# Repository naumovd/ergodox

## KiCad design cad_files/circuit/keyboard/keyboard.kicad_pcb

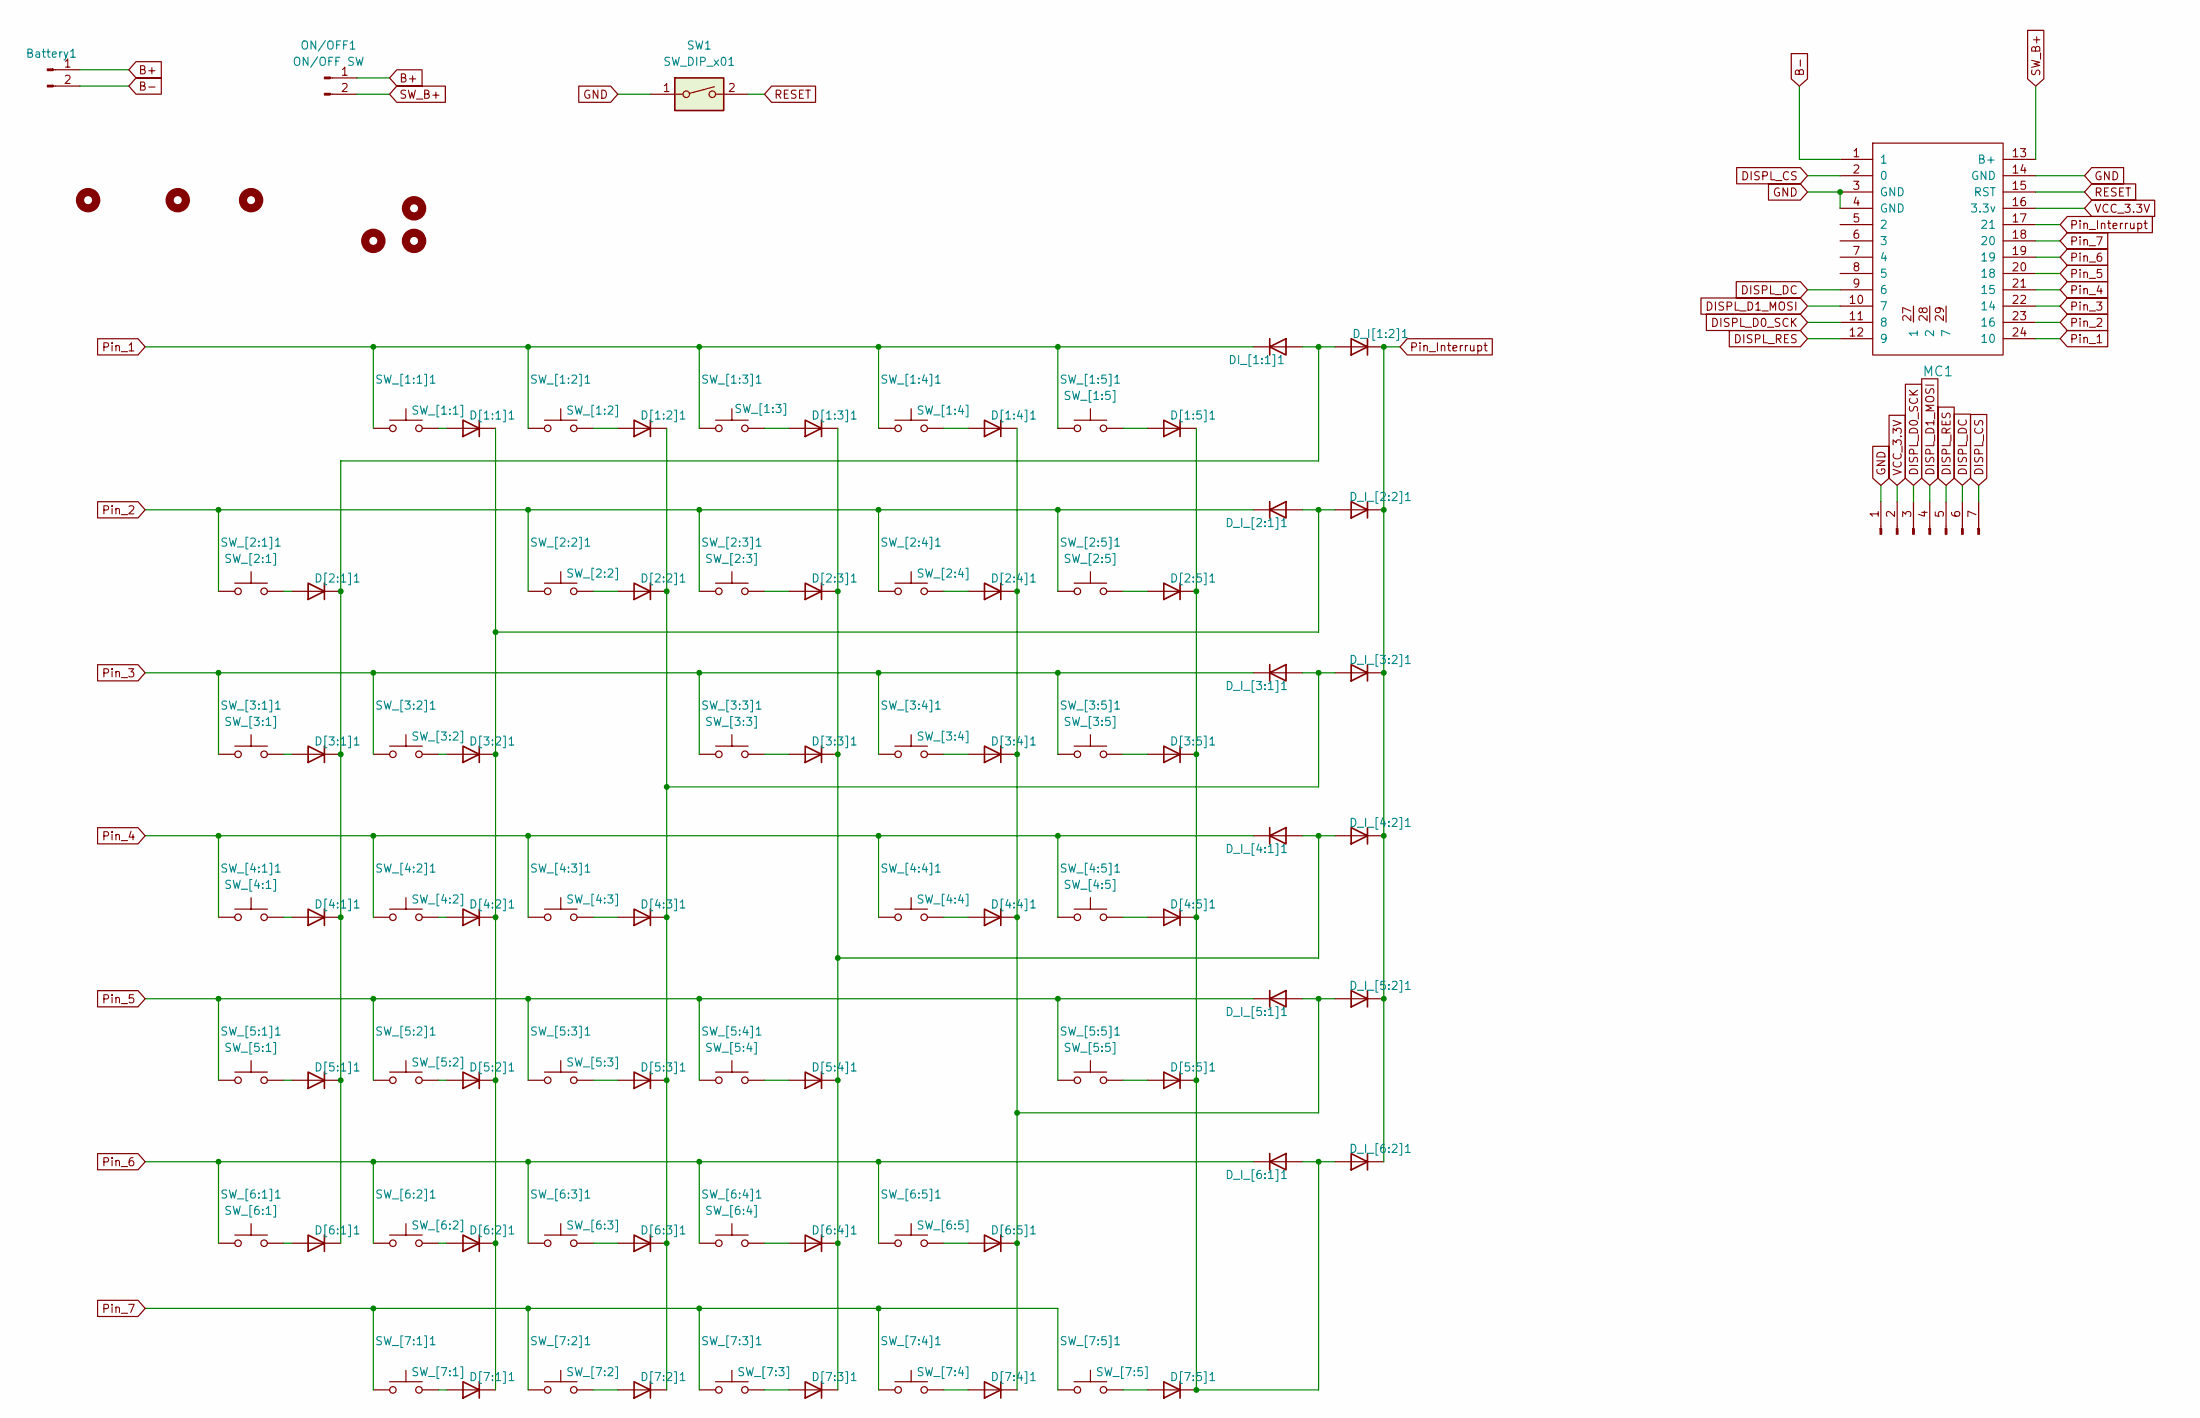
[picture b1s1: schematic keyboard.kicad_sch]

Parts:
Battery1: JST_PH_B2B-PH-K_1x02_P2.00mm_Vertical
DI_[1:1]1: Diode; D_T-1_P5.08mm_Horizontal
D[1:1]1, D[1:2]1, D[1:3]1, D[1:4]1, D[1:5]1, D[2:1]1, D[2:2]1, D[2:3]1, D[2:4]1, D[2:5]1, D[3:1]1, D[3:2]1, D[3:3]1, D[3:4]1, D[3:5]1, D[4:1]1, D[4:2]1, D[4:3]1, D[4:4]1, D[4:5]1, D[5:1]1, D[5:2]1, D[5:3]1, D[5:4]1, D[5:5]1, D[6:1]1, D[6:2]1, D[6:3]1, D[6:4]1, D[6:5]1, D[7:1]1, D[7:2]1, D[7:3]1, D[7:4]1, D[7:5]1: Diode; D_T-1_P5.08mm_Horizontal
D_I[1:2]1: Diode; D_T-1_P5.08mm_Horizontal
D_I_[2:1]1, D_I_[2:2]1, D_I_[3:1]1, D_I_[3:2]1, D_I_[4:1]1, D_I_[4:2]1, D_I_[5:1]1, D_I_[5:2]1, D_I_[6:1]1, D_I_[6:2]1: Diode; D_T-1_P5.08mm_Horizontal
Display1: PinHeader_1x07_P2.00mm_Vertical
H1, H2, H3, H5, H6, H7: MountingHole; MountingHole_2.2mm_M2_DIN965_Pad
MC1: Nice_Nano_V2; nice_nano_H_USBup
ON/OFF1: ON/OFF SW; JST_PH_B2B-PH-K_1x02_P2.00mm_Vertical
SW1: SW_DIP_x01; SW_PUSH_6mm_H4.3mm
SW_[1:1]1: SW_[1:1]; SW_MX_HS_KS-2P02B01-01_1u
SW_[1:2]1: SW_[1:2]; SW_MX_HS_KS-2P02B01-01_1u
SW_[1:3]1: SW_[1:3]; SW_MX_HS_KS-2P02B01-01_1u
SW_[1:4]1: SW_[1:4]; SW_MX_HS_KS-2P02B01-01_1u
SW_[1:5]1: SW_[1:5]; SW_MX_HS_KS-2P02B01-01_1u
SW_[2:1]1: SW_[2:1]; SW_MX_HS_KS-2P02B01-01_1u
SW_[2:2]1: SW_[2:2]; SW_MX_HS_KS-2P02B01-01_1u
SW_[2:3]1: SW_[2:3]; SW_MX_HS_KS-2P02B01-01_1u
SW_[2:4]1: SW_[2:4]; SW_MX_HS_KS-2P02B01-01_1u
SW_[2:5]1: SW_[2:5]; SW_MX_HS_KS-2P02B01-01_1u
SW_[3:1]1: SW_[3:1]; SW_MX_HS_KS-2P02B01-01_1u
SW_[3:2]1: SW_[3:2]; SW_MX_HS_KS-2P02B01-01_1u
SW_[3:3]1: SW_[3:3]; SW_MX_HS_KS-2P02B01-01_1u
SW_[3:4]1: SW_[3:4]; SW_MX_HS_KS-2P02B01-01_1u
SW_[3:5]1: SW_[3:5]; SW_MX_HS_KS-2P02B01-01_1u
SW_[4:1]1: SW_[4:1]; SW_MX_HS_KS-2P02B01-01_1u
SW_[4:2]1: SW_[4:2]; SW_MX_HS_KS-2P02B01-01_1u
SW_[4:3]1: SW_[4:3]; SW_MX_HS_KS-2P02B01-01_1u
SW_[4:4]1: SW_[4:4]; SW_MX_HS_KS-2P02B01-01_1u
SW_[4:5]1: SW_[4:5]; SW_MX_HS_KS-2P02B01-01_1u
SW_[5:1]1: SW_[5:1]; SW_MX_HS_KS-2P02B01-01_1u
SW_[5:2]1: SW_[5:2]; SW_MX_HS_KS-2P02B01-01_1u
SW_[5:3]1: SW_[5:3]; SW_MX_HS_KS-2P02B01-01_1u
SW_[5:4]1: SW_[5:4]; SW_MX_HS_KS-2P02B01-01_1u
SW_[5:5]1: SW_[5:5]; SW_MX_HS_KS-2P02B01-01_1u
SW_[6:1]1: SW_[6:1]; SW_MX_HS_KS-2P02B01-01_1u
SW_[6:2]1: SW_[6:2]; SW_MX_HS_KS-2P02B01-01_1u
SW_[6:3]1: SW_[6:3]; SW_MX_HS_KS-2P02B01-01_1u
SW_[6:4]1: SW_[6:4]; SW_MX_HS_KS-2P02B01-01_1u
SW_[6:5]1: SW_[6:5]; SW_MX_HS_KS-2P02B01-01_1u
SW_[7:1]1: SW_[7:1]; SW_MX_HS_KS-2P02B01-01_1u
SW_[7:2]1: SW_[7:2]; SW_MX_HS_KS-2P02B01-01_1u
SW_[7:3]1: SW_[7:3]; SW_MX_HS_KS-2P02B01-01_1u
SW_[7:4]1: SW_[7:4]; SW_MX_HS_KS-2P02B01-01_1u
SW_[7:5]1: SW_[7:5]; SW_MX_HS_KS-2P02B01-01_1u

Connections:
B+: Battery1.1, ON/OFF1.1
B-: Battery1.2, MC1.1; also elsewhere on the board
GND: Display1.1, MC1.3 (GND), MC1.4 (GND), MC1.14 (GND), SW1.1; also elsewhere on the board
unnamed: DI_[1:1]1.2 (A), D[2:1]1.1 (K), D[3:1]1.1 (K), D[4:1]1.1 (K), D[5:1]1.1 (K), D[6:1]1.1 (K), D_I[1:2]1.2 (A)
unnamed: D[1:1]1.2 (A), SW_[1:1]1.2
unnamed: D[1:1]1.1 (K), D[3:2]1.1 (K), D[4:2]1.1 (K), D[5:2]1.1 (K), D[6:2]1.1 (K), D[7:1]1.1 (K), D_I_[2:1]1.2 (A), D_I_[2:2]1.2 (A)
unnamed: D[1:2]1.2 (A), SW_[1:2]1.2
unnamed: D[1:2]1.1 (K), D[2:2]1.1 (K), D[4:3]1.1 (K), D[5:3]1.1 (K), D[6:3]1.1 (K), D[7:2]1.1 (K), D_I_[3:1]1.2 (A), D_I_[3:2]1.2 (A)
unnamed: D[1:3]1.2 (A), SW_[1:3]1.2
unnamed: D[1:3]1.1 (K), D[2:3]1.1 (K), D[3:3]1.1 (K), D[5:4]1.1 (K), D[6:4]1.1 (K), D[7:3]1.1 (K), D_I_[4:1]1.2 (A), D_I_[4:2]1.2 (A)
unnamed: D[1:4]1.2 (A), SW_[1:4]1.2
unnamed: D[1:4]1.1 (K), D[2:4]1.1 (K), D[3:4]1.1 (K), D[4:4]1.1 (K), D[6:5]1.1 (K), D[7:4]1.1 (K), D_I_[5:1]1.2 (A), D_I_[5:2]1.2 (A)
unnamed: D[1:5]1.2 (A), SW_[1:5]1.2
unnamed: D[1:5]1.1 (K), D[2:5]1.1 (K), D[3:5]1.1 (K), D[4:5]1.1 (K), D[5:5]1.1 (K), D[7:5]1.1 (K), D_I_[6:1]1.2 (A), D_I_[6:2]1.2 (A)
unnamed: D[2:1]1.2 (A), SW_[2:1]1.2
unnamed: D[2:2]1.2 (A), SW_[2:2]1.2
unnamed: D[2:3]1.2 (A), SW_[2:3]1.2
unnamed: D[2:4]1.2 (A), SW_[2:4]1.2
unnamed: D[2:5]1.2 (A), SW_[2:5]1.2
unnamed: D[3:1]1.2 (A), SW_[3:1]1.2
unnamed: D[3:2]1.2 (A), SW_[3:2]1.2
unnamed: D[3:3]1.2 (A), SW_[3:3]1.2
unnamed: D[3:4]1.2 (A), SW_[3:4]1.2
unnamed: D[3:5]1.2 (A), SW_[3:5]1.2
unnamed: D[4:1]1.2 (A), SW_[4:1]1.2
unnamed: D[4:2]1.2 (A), SW_[4:2]1.2
unnamed: D[4:3]1.2 (A), SW_[4:3]1.2
unnamed: D[4:4]1.2 (A), SW_[4:4]1.2
unnamed: D[4:5]1.2 (A), SW_[4:5]1.2
unnamed: D[5:1]1.2 (A), SW_[5:1]1.2
unnamed: D[5:2]1.2 (A), SW_[5:2]1.2
unnamed: D[5:3]1.2 (A), SW_[5:3]1.2
unnamed: D[5:4]1.2 (A), SW_[5:4]1.2
unnamed: D[5:5]1.2 (A), SW_[5:5]1.2
unnamed: D[6:1]1.2 (A), SW_[6:1]1.2
unnamed: D[6:2]1.2 (A), SW_[6:2]1.2
unnamed: D[6:3]1.2 (A), SW_[6:3]1.2
unnamed: D[6:4]1.2 (A), SW_[6:4]1.2
unnamed: D[6:5]1.2 (A), SW_[6:5]1.2
unnamed: D[7:1]1.2 (A), SW_[7:1]1.2
unnamed: D[7:2]1.2 (A), SW_[7:2]1.2
unnamed: D[7:3]1.2 (A), SW_[7:3]1.2
unnamed: D[7:4]1.2 (A), SW_[7:4]1.2
unnamed: D[7:5]1.2 (A), SW_[7:5]1.2
unnamed: Display1.2, MC1.16 (3.3v)
unnamed: Display1.3, MC1.11 (8)
unnamed: Display1.4, MC1.10 (7)
unnamed: Display1.5, MC1.12 (9)
unnamed: Display1.6, MC1.9 (6)
unnamed: Display1.7, MC1.2 (0)
Pin_1: DI_[1:1]1.1 (K), MC1.24 (10), SW_[1:1]1.1, SW_[1:2]1.1, SW_[1:3]1.1, SW_[1:4]1.1, SW_[1:5]1.1; also elsewhere on the board
Pin_2: D_I_[2:1]1.1 (K), MC1.23 (16), SW_[2:1]1.1, SW_[2:2]1.1, SW_[2:3]1.1, SW_[2:4]1.1, SW_[2:5]1.1; also elsewhere on the board
Pin_3: D_I_[3:1]1.1 (K), MC1.22 (14), SW_[3:1]1.1, SW_[3:2]1.1, SW_[3:3]1.1, SW_[3:4]1.1, SW_[3:5]1.1; also elsewhere on the board
Pin_4: D_I_[4:1]1.1 (K), MC1.21 (15), SW_[4:1]1.1, SW_[4:2]1.1, SW_[4:3]1.1, SW_[4:4]1.1, SW_[4:5]1.1; also elsewhere on the board
Pin_5: D_I_[5:1]1.1 (K), MC1.20 (18), SW_[5:1]1.1, SW_[5:2]1.1, SW_[5:3]1.1, SW_[5:4]1.1, SW_[5:5]1.1; also elsewhere on the board
Pin_6: D_I_[6:1]1.1 (K), MC1.19, SW_[6:1]1.1, SW_[6:2]1.1, SW_[6:3]1.1, SW_[6:4]1.1, SW_[6:5]1.1; also elsewhere on the board
Pin_7: MC1.18 (20), SW_[7:1]1.1, SW_[7:2]1.1, SW_[7:3]1.1, SW_[7:4]1.1, SW_[7:5]1.1; also elsewhere on the board
Pin_Interrupt: D_I[1:2]1.1 (K), D_I_[2:2]1.1 (K), D_I_[3:2]1.1 (K), D_I_[4:2]1.1 (K), D_I_[5:2]1.1 (K), D_I_[6:2]1.1 (K), MC1.17 (21); also elsewhere on the board
RESET: MC1.15 (RST), SW1.2; also elsewhere on the board
SW_B+: MC1.13 (B+), ON/OFF1.2; also elsewhere on the board

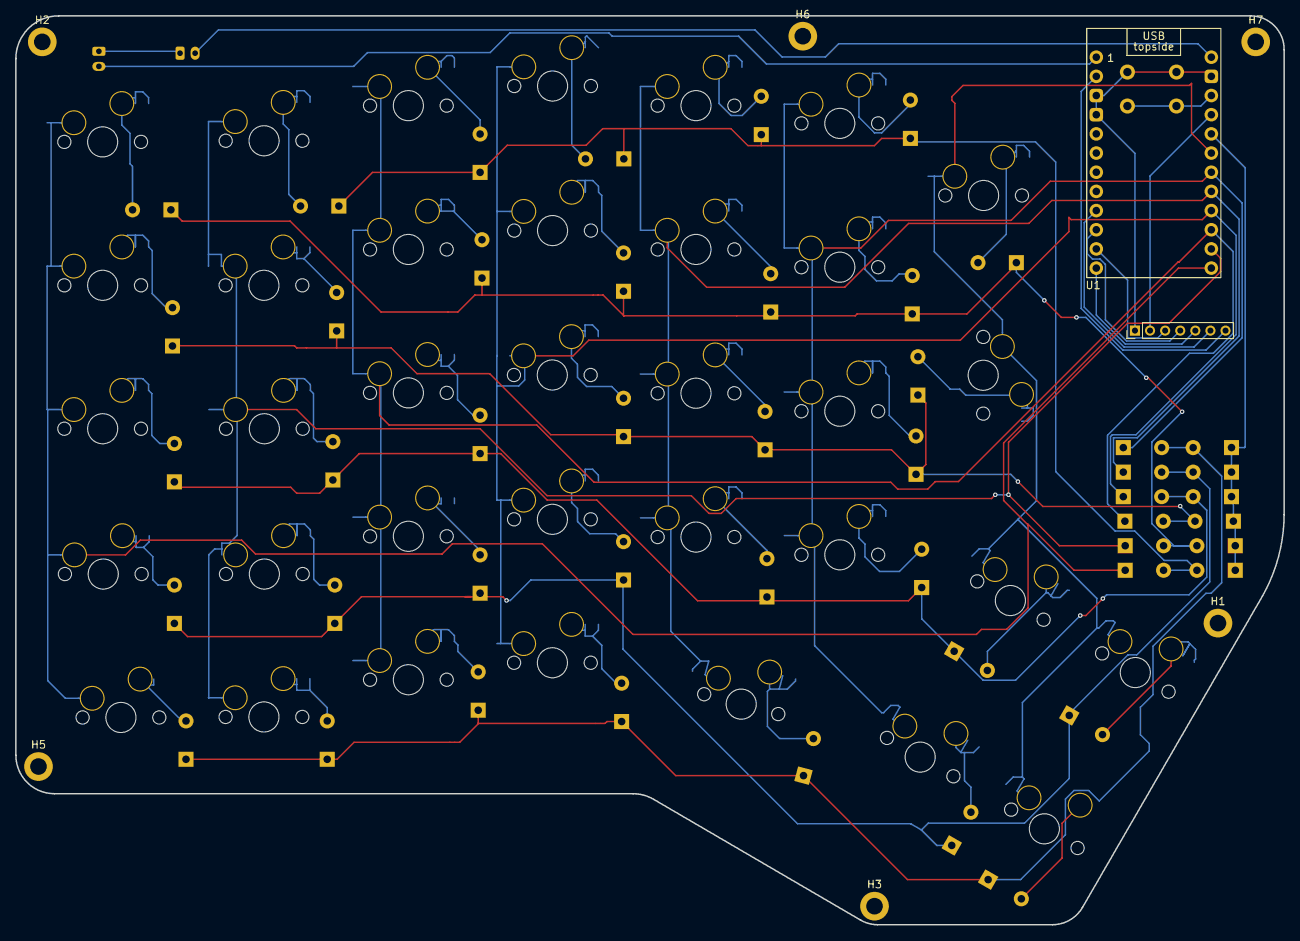
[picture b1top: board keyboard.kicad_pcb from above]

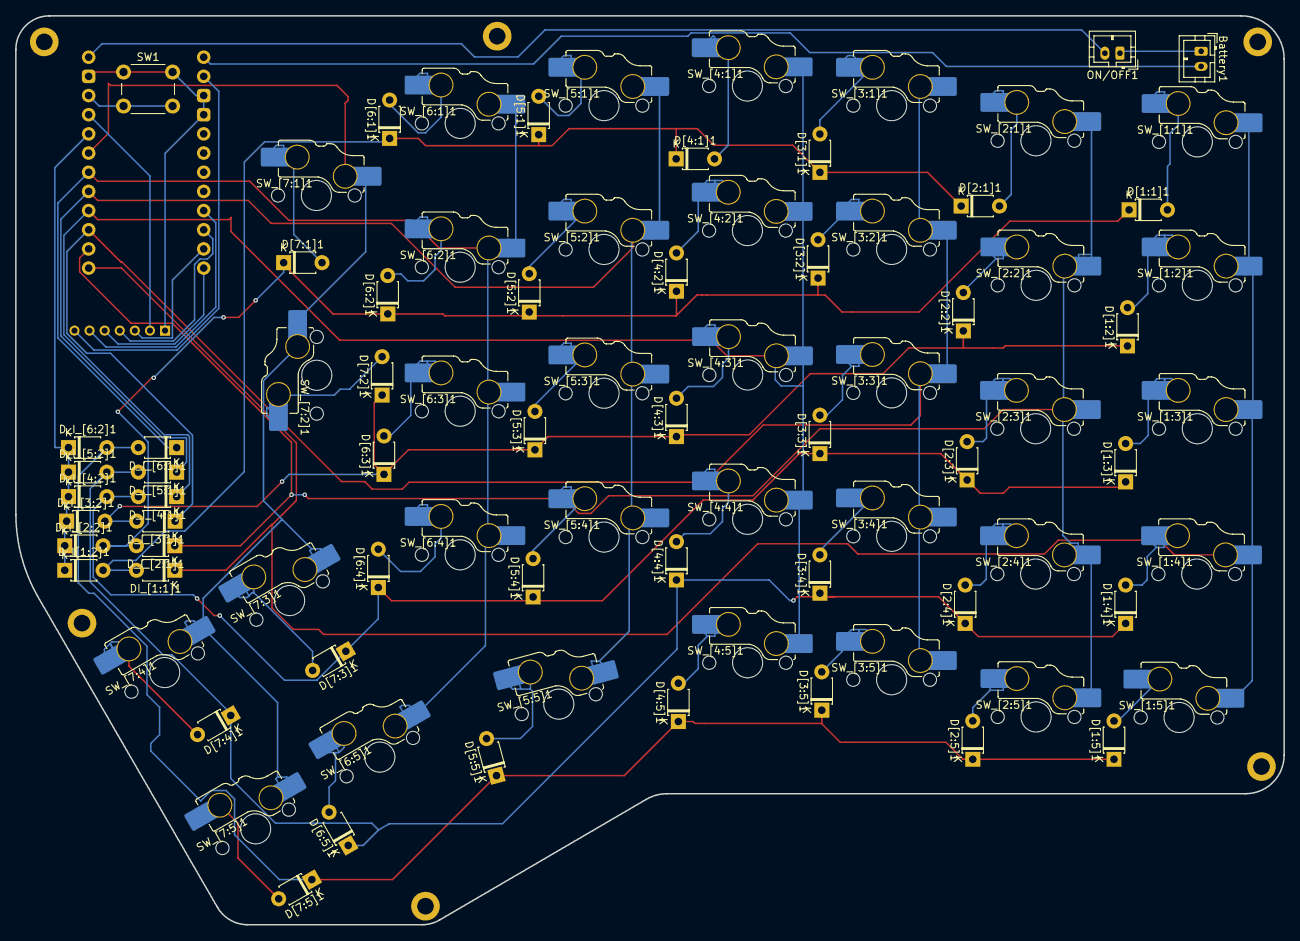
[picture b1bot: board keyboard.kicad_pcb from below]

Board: 2 copper layers, 168.0 x 120.4 mm, 93 parts (85 on the bottom side), 60 nets.

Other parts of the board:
Display: Display; PinHeader_1x07_P2.00mm_Vertical
U1: Nice_Nano_V2; nice_nano_H_USBup

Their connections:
B-: U1.1; also elsewhere on the board
DISPL_CS: Display.7, U1.2 (0)
DISPL_D0_SCK: Display.3, U1.11 (8)
DISPL_D1_MOSI: Display.4, U1.10 (7)
DISPL_DC: Display.6, U1.9 (6)
DISPL_RES: Display.5, U1.12 (9)
GND: Display.1, U1.3 (GND), U1.4 (GND), U1.14 (GND); also elsewhere on the board
Pin_1: U1.24 (10); also elsewhere on the board
Pin_2: U1.23 (16); also elsewhere on the board
Pin_3: U1.22 (14); also elsewhere on the board
Pin_4: U1.21 (15); also elsewhere on the board
Pin_5: U1.20 (18); also elsewhere on the board
Pin_6: U1.19; also elsewhere on the board
Pin_7: U1.18 (20); also elsewhere on the board
Pin_Interrupt: U1.17 (21); also elsewhere on the board
RESET: U1.15 (RST); also elsewhere on the board
SW_B+: U1.13 (B+); also elsewhere on the board
VCC_3.3V: Display.2, U1.16 (3.3v)

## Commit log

2024-06-14 Default debug commit message
2024-06-18 Added kicad project
2024-06-21 Set GPIO 6 to ground
2025-02-26 Added left KB cad files
2025-03-06 Updated the keyboard sketches. Fully buildable without errors
2025-03-08 Updated wires channel
2025-03-19 Finished right
2025-03-19 finished right KB
2025-04-03 Added cad files
2025-04-05 Cad files finished
2025-04-14 Added arrow controls to the 2 layer
2025-04-17 Updated keymap. Increaseed debounce
2025-04-23 Keymap update
2025-04-27 Energy config update
2025-04-27 Change the keyboard name
